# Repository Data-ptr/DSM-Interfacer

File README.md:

# DSM-Interfacer
 A FOSS (Free Open Source Software) and Open Hardware project for a DIAG/OBD1 interface board for DSMs

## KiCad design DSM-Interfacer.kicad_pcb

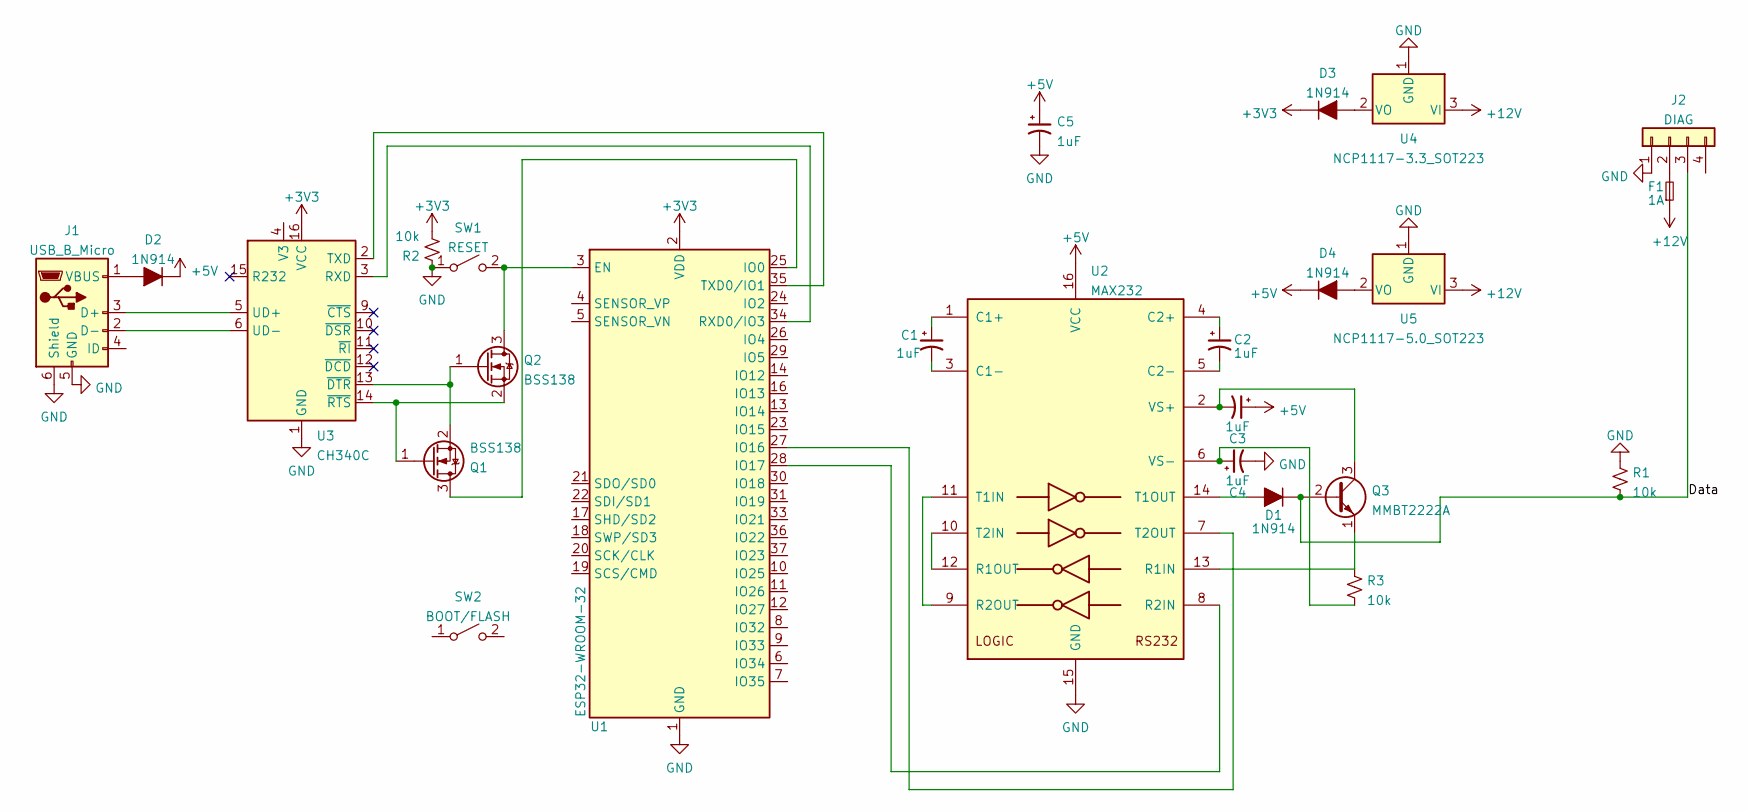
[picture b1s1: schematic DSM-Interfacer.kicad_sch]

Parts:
C1, C2, C3, C4, C5: 1uF; C_1206_3216Metric
D1, D2, D3, D4: 1N914; D_1206_3216Metric
F1: 1A; Fuse_1206_3216Metric
J1: USB_B_Micro; USB_Micro-B_Wuerth_629105150521
J2: DIAG; PinHeader_1x04_P2.54mm_Vertical
Q1, Q2: BSS138; SOT-23
Q3: MMBT2222A; SOT-23
R1, R2, R3: 10k; R_1206_3216Metric
SW1: RESET; SW_SPST_B3S-1000
SW2: BOOT/FLASH; SW_SPST_B3S-1000
U1: ESP32-WROOM-32
U2: MAX232; SOIC-16_3.9x9.9mm_P1.27mm
U3: CH340C; SOIC-16_3.9x9.9mm_P1.27mm
U4: NCP1117-3.3_SOT223; SOT-223-3_TabPin2
U5: NCP1117-5.0_SOT223; SOT-223-3_TabPin2

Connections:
+3V3: D3.1 (K), R2.1, U1.2 (VDD), U3.16 (VCC)
+5V: C3.1, C5.1, D2.1 (K), D4.1 (K), U2.16 (VCC)
+12V: F1.1, U4.3 (VI), U5.3 (VI)
/Data: D1.1 (K), J2.3, Q3.2 (B), R1.2
GND: C4.2, C5.2, J1.5 (GND), J1.6 (Shield), J2.1, R1.1, R2.2, SW1.1 (A), U1.1 (GND), U1.15 (GND), U1.38 (GND), U1.39 (GND), U2.15 (GND), U3.1 (GND), U4.1 (GND), U5.1 (GND)
unnamed: C1.1, U2.1 (C1+)
unnamed: C1.2, U2.3 (C1-)
unnamed: C2.1, U2.4 (C2+)
unnamed: C2.2, U2.5 (C2-)
unnamed: C3.2, Q3.3 (C), U2.2 (VS+)
unnamed: C4.1, R3.2, U2.6 (VS-)
unnamed: D1.2 (A), U2.14 (T1OUT)
unnamed: D2.2 (A), J1.1 (VBUS)
unnamed: D3.2 (A), U4.2 (VO)
unnamed: D4.2 (A), U5.2 (VO)
unnamed: F1.2, J2.2
unnamed: J1.2 (D-), U3.6 (UD-)
unnamed: J1.3 (D+), U3.5 (UD+)
unnamed: Q1.1 (G), Q2.2 (S), U3.14 (~RTS)
unnamed: Q1.2 (S), Q2.1 (G), U3.13 (~DTR)
unnamed: Q1.3 (D), U1.25 (IO0)
unnamed: Q2.3 (D), SW1.2 (B), U1.3 (EN)
unnamed: Q3.1 (E), R3.1, U2.13 (R1IN)
unnamed: U1.27 (IO16), U2.7 (T2OUT)
unnamed: U1.28 (IO17), U2.8 (R2IN)
unnamed: U1.34 (RXD0/IO3), U3.3 (RXD)
unnamed: U1.35 (TXD0/IO1), U3.2 (TXD)
unnamed: U2.10 (T2IN), U2.12 (R1OUT)
unnamed: U2.9 (R2OUT), U2.11 (T1IN)

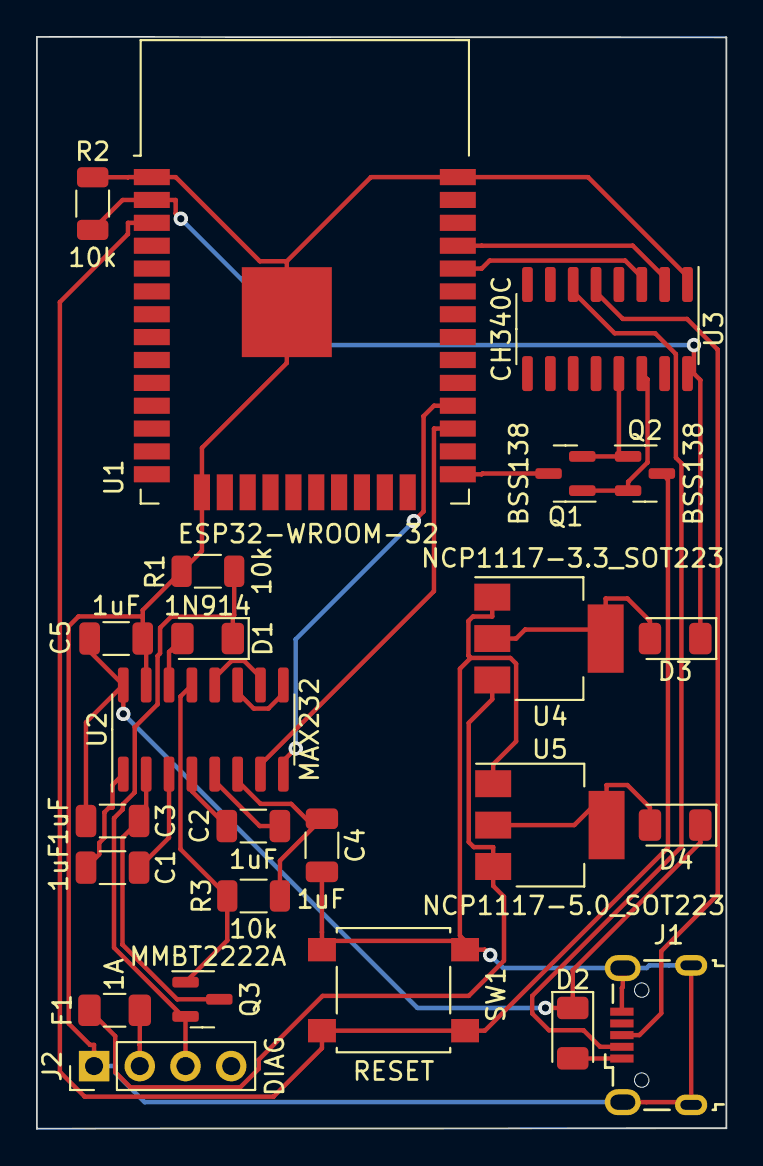
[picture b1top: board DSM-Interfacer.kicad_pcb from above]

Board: 2 copper layers, 38.3 x 60.7 mm, 24 parts (0 on the bottom side), 29 nets.

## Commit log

2022-03-01 Init commit
2022-03-01 smaller MAX323
